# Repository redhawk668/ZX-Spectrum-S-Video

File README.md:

# Introduction

This PCB replaces the RF modulatorbox on a Sinclair ZX Spectrum computer. It's main purpose is to improve the video output of the ZX Spectrum by seperating the luma/sync (Y) and chroma (C) signals to get rid of the dotcrawl.

# Composite output works, why designing this board?
Why not? I use a RetroTink 2X (https://www.retrotink.com/product-page/retrotink-2x), this little device converts an analog signal to HDMI output. The Spectrum's composite output is absolutely horrible on this. The RetroTink provides an s-video input, that gave me the idea to seperate the Y/C signals to convert the composite output to s-video, improving the video signal. Some googling later I found this thread on the World of Spectrum forums: 

https://www.worldofspectrum.org/forums/discussion/47120/new-video-about-s-video-modification-on-issue-two-48k-spectrum/p1. 

(Credits to MAK1024 and RGA24 for providing the basics for this design).

# The PCB itself

# Rev. A - Simple through hole design (first design)

# Rev. D01 - Final design

Rev. A is a through hole design and uses transistors to amplify the signal. 

Rev. D01 is the final design and like the previous Rev. D, based on the THS7314D chip. Two resistors have been removed, this was causing a dim picture on some displays. This design is also a 4-layer with seperated ground/power planes. For the connection to the ZX Spectrum a JST connector is used.

I have included the Gerber files from each design, so you can have the PCB of your choice manufactured by your preferred manufacturer.

# Billing of Materials: Rev. A
- 1x 4 pin mini din chassis (Lumberg TM 0508 A/4)
- 3x NPN Transistors. I've used BC547, but most small signal transistors should be fine.
- 1x 2K2 Resistor
- 1x 3K9 or 1x 4K3 Resistor
- 1x 390R Resistor
- 1x 22uF Electrolytic Capacitor

# Billing of Materials: Rev. D.01 (Final Design)
- J1: 1x 4 pin mini din chassis (Lumberg TM 0508 A/4)
- Q1: BC847, SOT323/SC70
- U1: THS7314D, SOIC-8
- C1: 0,1 uF ceramic capacitor XR7, 0805
- C2: 0,1 uF ceramic capacitor XR7, 0805
- C3: 0,1 uF ceramic capacitor XR7, 0805
- C65: 22 uF aluminium electrolytic capacitor (6,3x5,3)
- R1: 1K thick film resistor, 0805
- R2: 390R thick film resistor, 0805
- R3: 2K2 thick film resistor, 0805
- R4: 75R thick film resistor, 0805
- R5: 75R thick film resistor, 0805
- J2: 3x01 JST connector 2.54mm spacing

# For Rev. A designs (Rev D.01 has JST connector):

- Some wire
- 2x M2.5 screws
- 4x M2.5 nuts

# Summary
Once you have built the little circuit, solder in wires for luma in, chroma in and +5 volt in. Make the wires for luma in and +5 volt about 50mm. PCB layout on an Issue 2 is a bit different than Issue 3 and above. 50mm for the chroma wire should be long enough for an Issue 2. Issue 3 and above needs a bit longer wire. 

Now, carefully remove the modulatorbox and capacitor C65 from the Spectrum PCB. Now carefully mount the PCB onto the Spectrum PCB using the screws and nuts (might need drilling, but M2.5 should fit). Seperate the PCB's using one of the nuts on either side. Tighten the PCB to the Spectrum PCB using a nut on either side, as shown in the picture:

Now solder the luma and +5 volt into their respective holes. (The composite output on the Spectrum is now the luma output). Solder the chroma wire into the the + side of capacitor C65. On Issue 2 PCB's C65 is underneath the modulator box, on Issue 3 boards and above, C65 is above C25 on the left side of the PCB.

# Issue 2:

# Issue 3 and above:

# Rev. D01 connection to ZX Spectrum:

I recommend cutting the pins of the mini din chassis as close to the underside of the PCB as possible, to prevent short circuits. 

# Disclaimer
I am not responsible for any damage to your Spectrum, you do this at your own risk. Take care when you build this and when fitting it to your Spectrum.

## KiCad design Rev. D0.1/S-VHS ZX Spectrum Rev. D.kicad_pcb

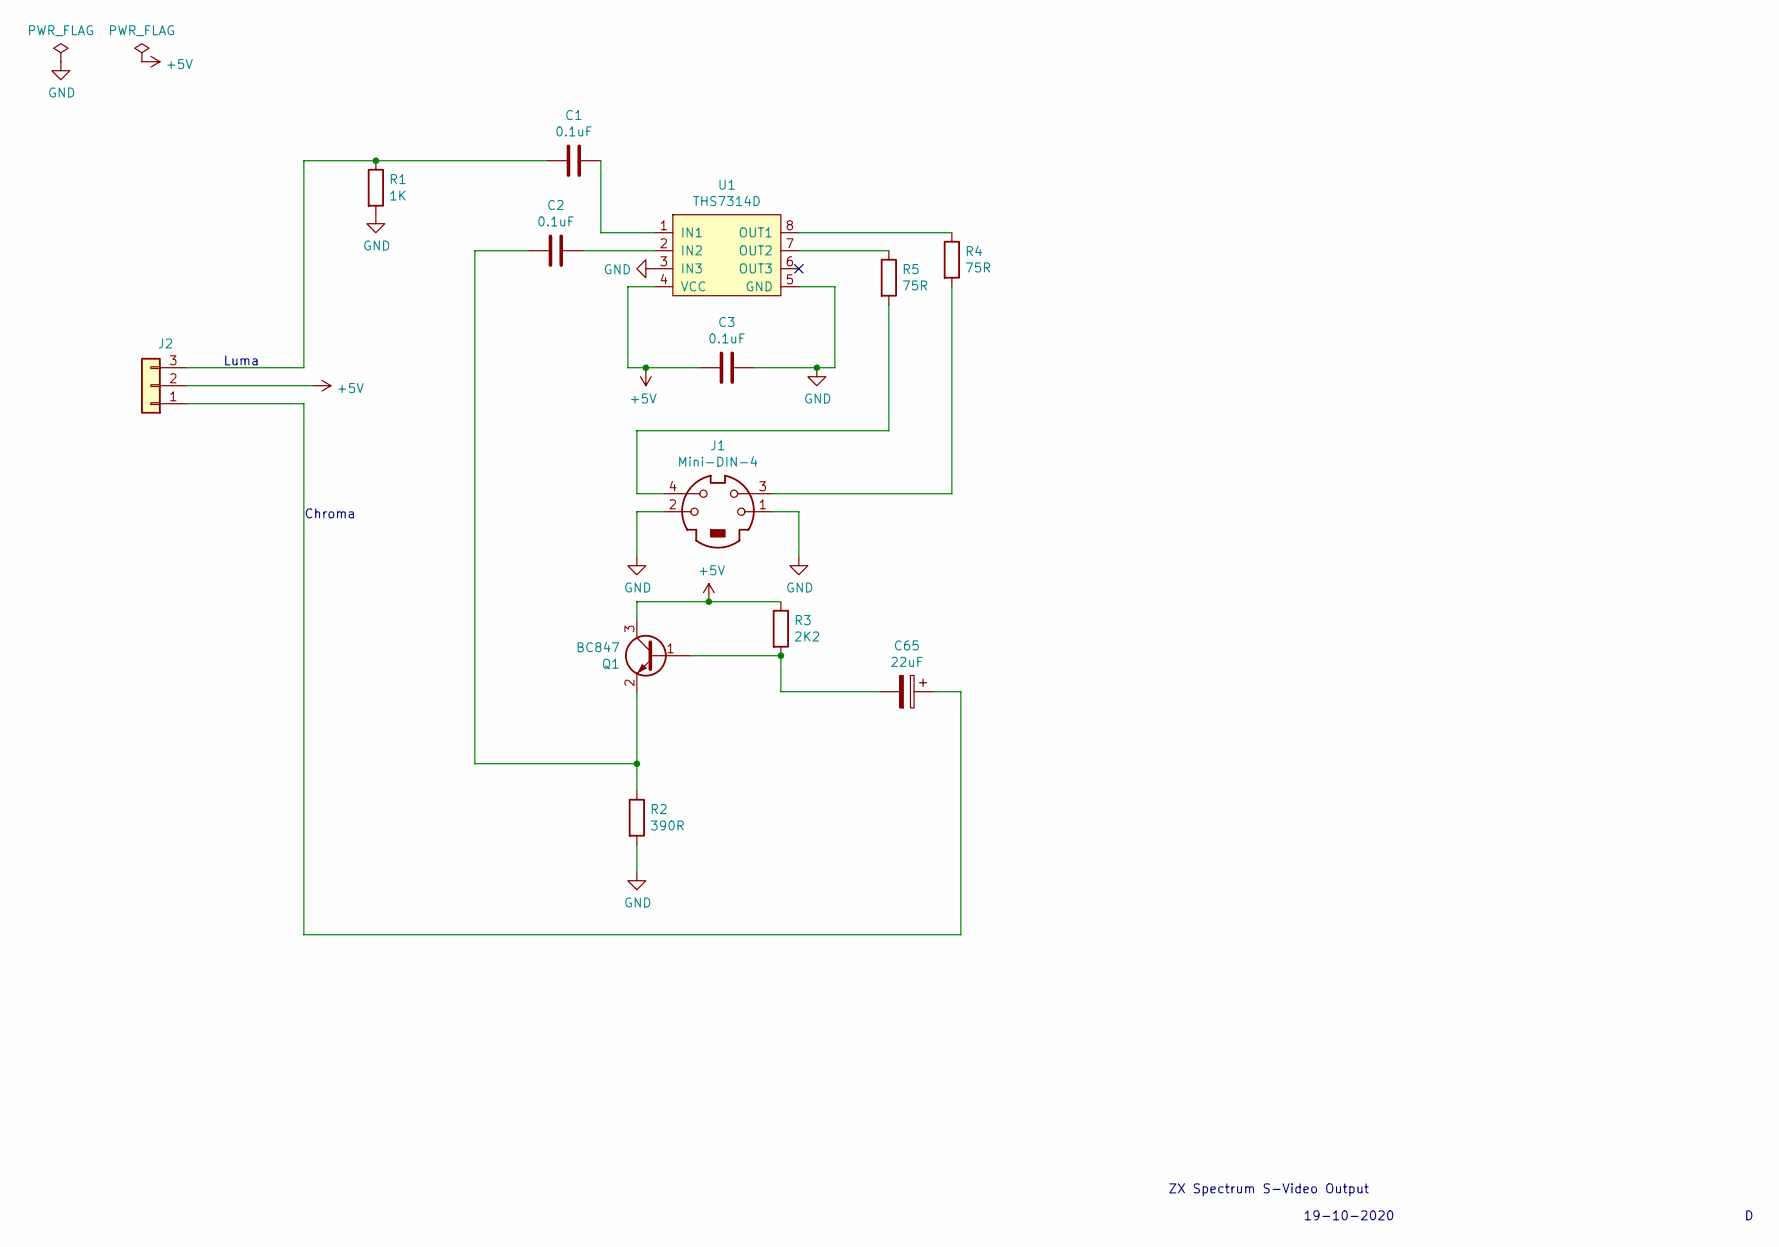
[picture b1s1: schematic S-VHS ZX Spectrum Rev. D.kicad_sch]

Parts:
C1, C2, C3: 0.1uF; C_0805_2012Metric_Pad1.18x1.45mm_HandSolder
C65: 22uF; CP_Elec_6.3x5.3
J1: Mini-DIN-4; MD40SMK
J2: Conn_01x03; JST_EH_B3B-EH-A_1x03_P2.50mm_Vertical
Q1: BC847; SOT-323_SC-70_Handsoldering
R1: 1K; R_0805_2012Metric_Pad1.20x1.40mm_HandSolder
R2: 390R; R_0805_2012Metric_Pad1.20x1.40mm_HandSolder
R3: 2K2; R_0805_2012Metric_Pad1.20x1.40mm_HandSolder
R4, R5: 75R; R_0805_2012Metric_Pad1.20x1.40mm_HandSolder
U1: THS7314D; SOIC-8_3.9x4.9mm_P1.27mm

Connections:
+5V: C3.1, J2.2, Q1.3 (C), R3.1, U1.4 (VCC)
GND: C3.2, J1.1, J1.2, R1.2, R2.2, U1.3 (IN3), U1.5 (GND); also elsewhere on the board
unnamed: C1.1, U1.1 (IN1)
unnamed: C1.2, J2.3, R1.1
unnamed: C2.1, U1.2 (IN2)
unnamed: C2.2, Q1.2 (E), R2.1
unnamed: C65.1, J2.1
unnamed: C65.2, Q1.1 (B), R3.2
unnamed: J1.3, R4.2
unnamed: J1.4, R5.2
unnamed: R4.1, U1.8 (OUT1)
unnamed: R5.1, U1.7 (OUT2)

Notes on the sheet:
Chroma
Luma
19-10-2020
ZX Spectrum S-Video Output

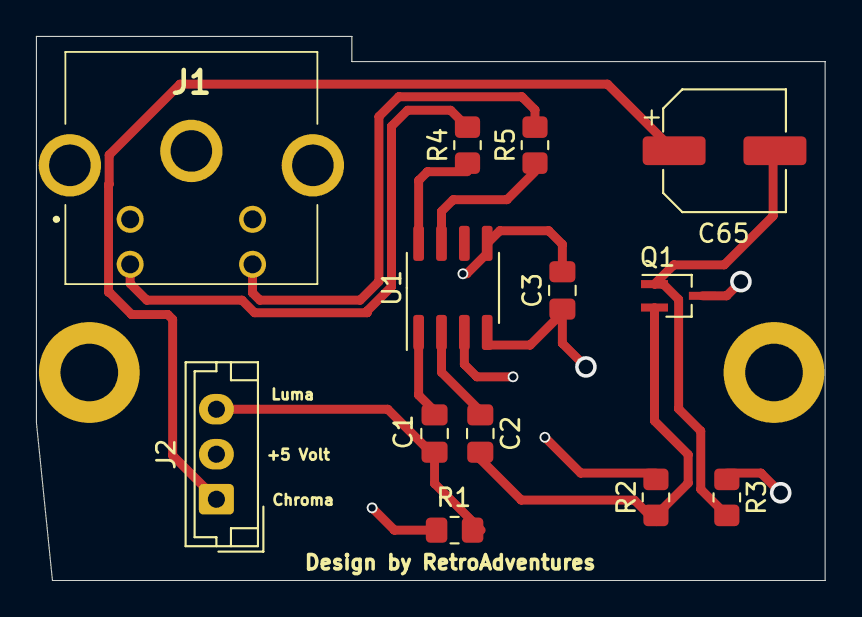
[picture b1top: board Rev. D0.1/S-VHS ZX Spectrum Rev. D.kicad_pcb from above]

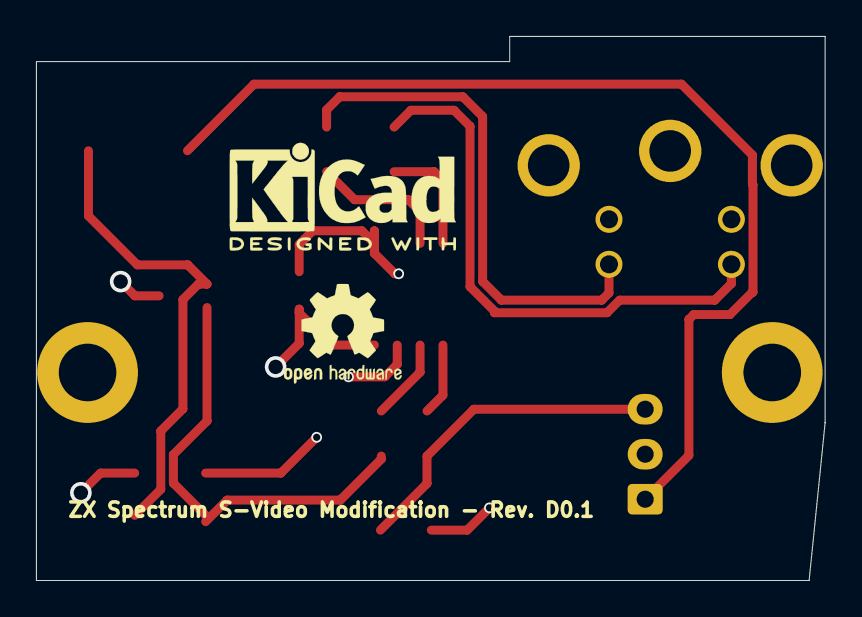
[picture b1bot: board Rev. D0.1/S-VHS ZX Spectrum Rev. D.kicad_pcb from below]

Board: 4 copper layers, 43.8 x 30.2 mm, 17 parts (2 on the bottom side), 12 nets.

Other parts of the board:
KiCad Logo: KiCad-Logo2_6mm_SilkScreen
Left MountHole: MountingHole_3.2mm_M3_DIN965_Pad
Open Hardware Logo: OSHW-Logo2_7.3x6mm_SilkScreen
Right MountHole: MountingHole_3.2mm_M3_DIN965_Pad

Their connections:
GND: Left MountHole.1, Right MountHole.1; also elsewhere on the board

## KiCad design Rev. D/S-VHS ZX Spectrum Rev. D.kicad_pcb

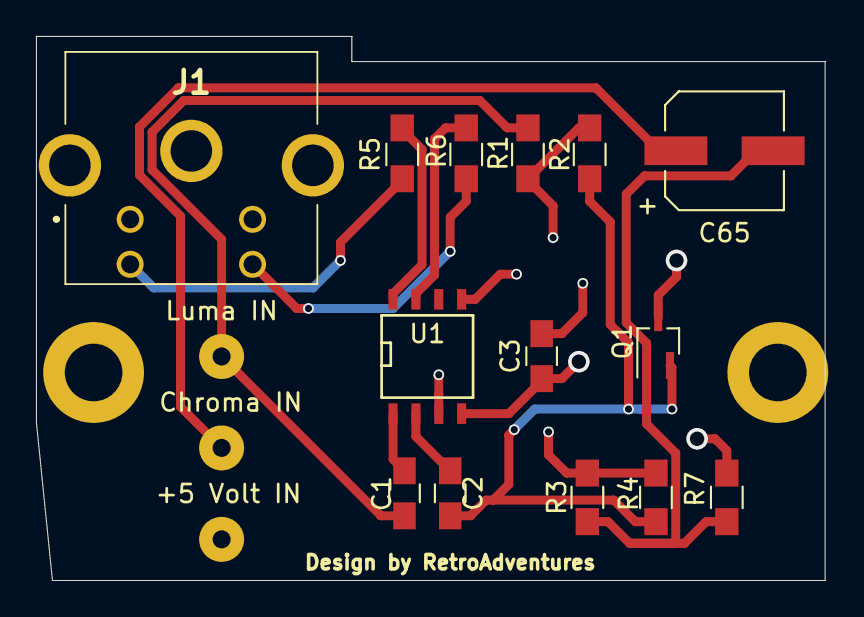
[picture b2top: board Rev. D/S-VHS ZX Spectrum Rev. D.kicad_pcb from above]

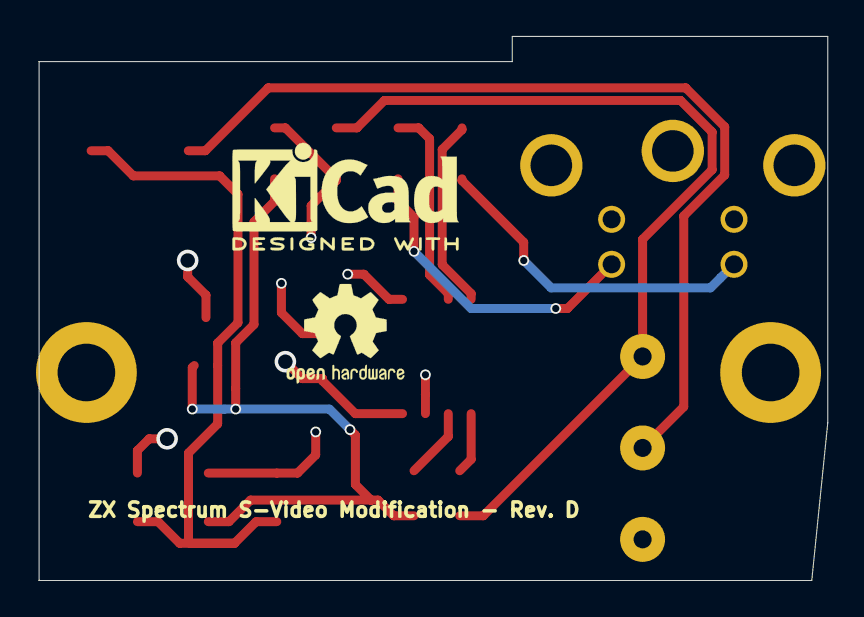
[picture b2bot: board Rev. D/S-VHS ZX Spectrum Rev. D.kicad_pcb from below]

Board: 4 copper layers, 43.8 x 30.2 mm, 21 parts (2 on the bottom side), 12 nets.

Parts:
+5 Volt IN: +5 Volt In; SolderWirePad_single_1mmDrill
C1, C2, C3: 0.1uF; C_0805_HandSoldering
C65: 22uF; CP_Elec_6.3x5.3
Chroma IN: Chroma Input; SolderWirePad_single_1mmDrill
J1: Mini-DIN-4; MD40SMK
KiCad Logo: KiCad-Logo2_6mm_SilkScreen
Left MountHole: MountingHole_3.2mm_M3_DIN965_Pad
Luma IN: Luma Input; SolderWirePad_single_1mmDrill
Open Hardware Logo: OSHW-Logo2_7.3x6mm_SilkScreen
Q1: BC847; SOT-323_SC-70_Handsoldering
R1, R2: 1K; R_0805_HandSoldering
R3: 4.3K; R_0805_HandSoldering
R4: 390R; R_0805_HandSoldering
R5, R6: 75R; R_0805_HandSoldering
R7: 2K2; R_0805_HandSoldering
Right MountHole: MountingHole_3.2mm_M3_DIN965_Pad
U1: THS7314D; SOIC-8-N

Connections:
+5V: +5 Volt IN.1, C3.1, Q1.3, R7.1, U1.4
GND: C3.2, J1.1, J1.2, Left MountHole.1, R1.2, R2.2, R3.2, R4.2, Right MountHole.1, U1.3, U1.5
unnamed: C1.1, U1.1
unnamed: C1.2, Luma IN.1, R1.1
unnamed: C2.1, U1.2
unnamed: C2.2, Q1.2, R2.1, R4.1
unnamed: C65.1, Chroma IN.1
unnamed: C65.2, Q1.1, R3.1, R7.2
unnamed: J1.3, R5.2
unnamed: J1.4, R6.2
unnamed: R5.1, U1.8
unnamed: R6.1, U1.7

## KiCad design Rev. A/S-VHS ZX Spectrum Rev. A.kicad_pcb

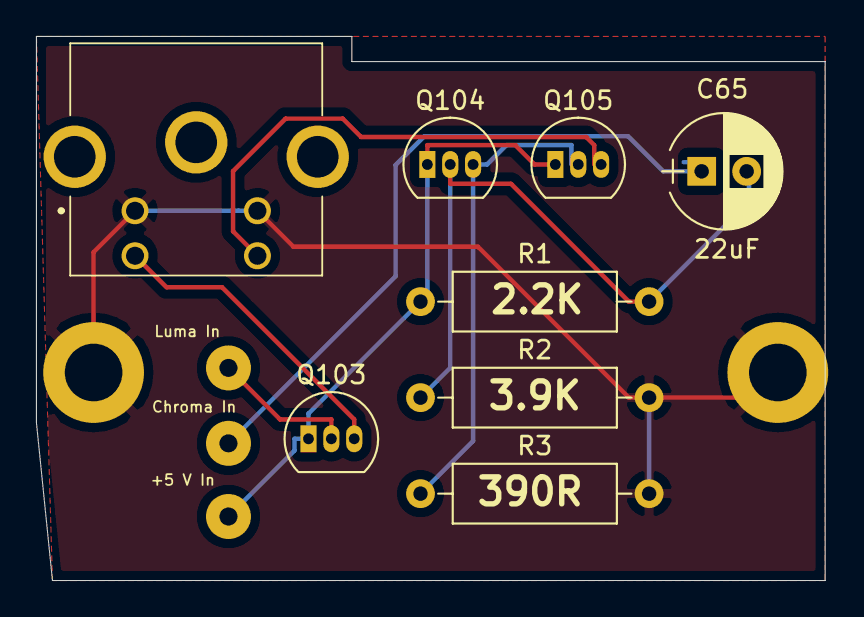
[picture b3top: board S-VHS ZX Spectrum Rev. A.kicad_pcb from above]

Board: 2 copper layers, 43.8 x 30.2 mm, 13 parts (0 on the bottom side), 8 nets.

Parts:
C65: 22uF; CP_Radial_D6.3mm_P2.50mm
J1: Mini-DIN-4; MD40SMK
J2, J3, J4: SolderWirePad_single_1mmDrill
Q103, Q104, Q105: BC547; TO-92_Inline_Narrow_Oval
R1: 2.2K; R_Axial_DIN0309_L9.0mm_D3.2mm_P12.70mm_Horizontal
R2: 3.9K; R_Axial_DIN0309_L9.0mm_D3.2mm_P12.70mm_Horizontal
R3: 390R; R_Axial_DIN0309_L9.0mm_D3.2mm_P12.70mm_Horizontal
REF1, REF2: MountingHole_3.2mm_M3_DIN965_Pad

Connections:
+5V: J4.1, Q103.1, Q104.1, Q105.1, R1.1
GND: J1.1, J1.2, R2.2, R3.2, REF1.1, REF2.1
unnamed: C65.1, J3.1
unnamed: C65.2, Q104.2, R1.2, R2.1
unnamed: J1.3, Q103.3
unnamed: J1.4, Q105.3
unnamed: J2.1, Q103.2
unnamed: Q104.3, Q105.2, R3.1

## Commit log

2020-05-23 Create LICENSE
2020-07-01 Add files via upload
    This is the final Revision.
